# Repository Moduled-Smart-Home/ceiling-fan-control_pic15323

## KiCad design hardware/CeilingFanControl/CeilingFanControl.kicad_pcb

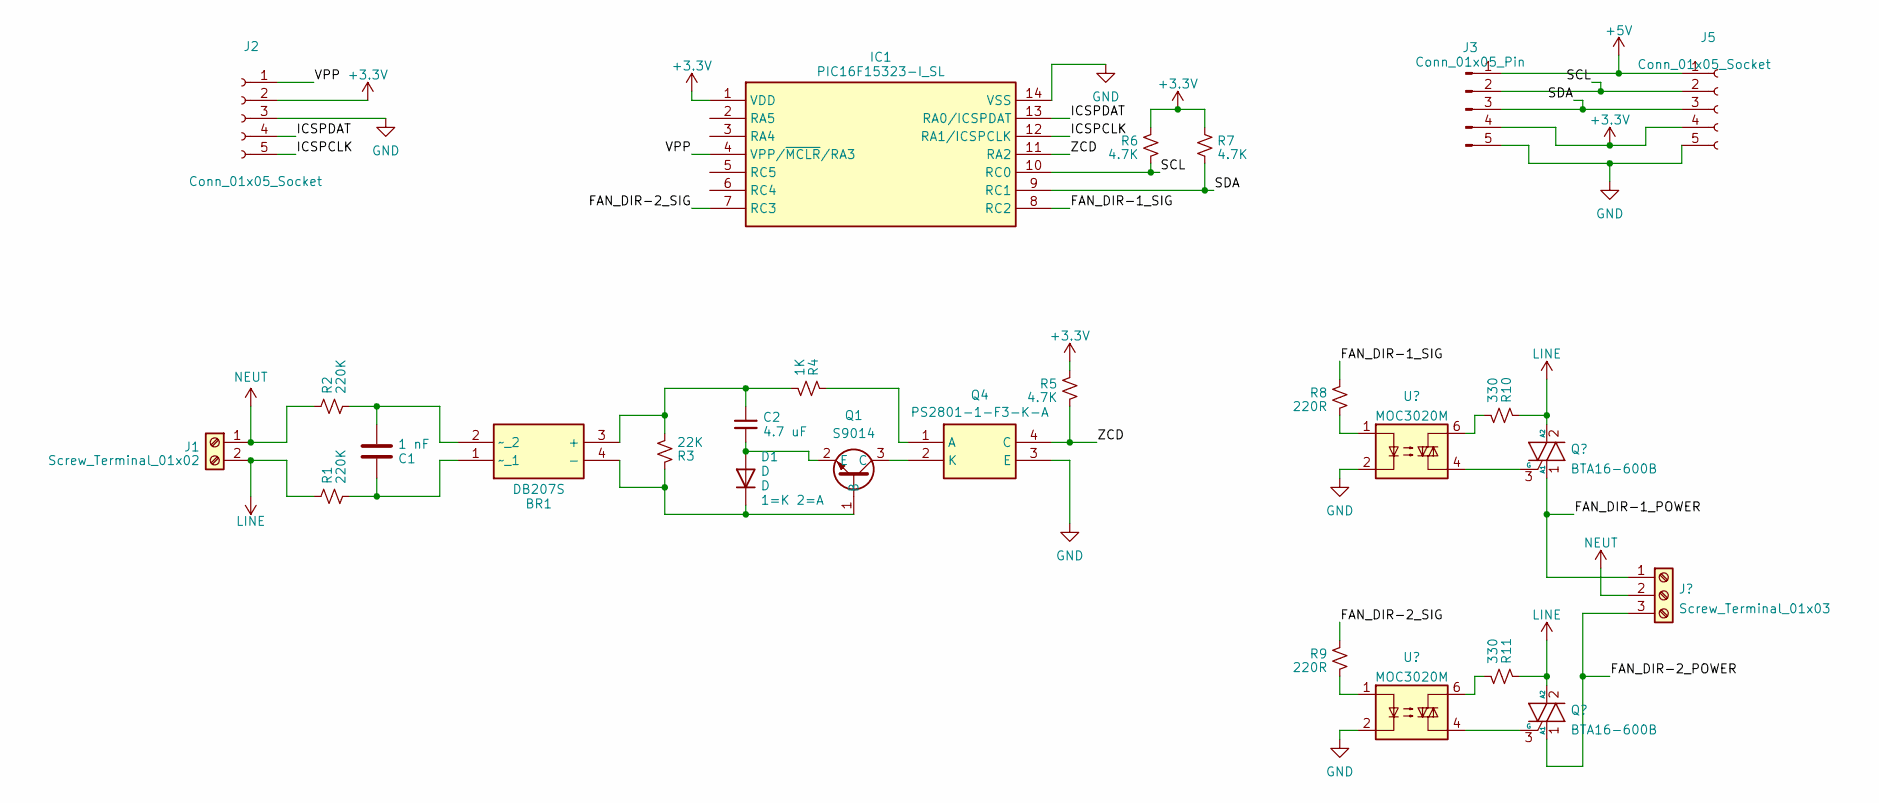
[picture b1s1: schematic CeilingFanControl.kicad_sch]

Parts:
BR1: DB207S; SOP510P1015X375-4N; Manufacturer_Part_Number DB207S
C1: 1 nF; C_0805_2012Metric
C2: 4.7 uF; C_0805_2012Metric
D1: D; D_SOD-123
IC1: PIC16F15323-I_SL; SOIC127P600X175-14N; Manufacturer_Part_Number PIC16F15323-I/SL; Mouser Part Number 579-PIC16F15323-I/SL
J1: Screw_Terminal_01x02; KF3012P
J2: Conn_01x05_Socket; PinHeader_1x05_P2.54mm_Vertical
J3: Conn_01x05_Pin; PinHeader_1x05_P2.54mm_Horizontal
J4: Screw_Terminal_01x03; KF3013P
J5: Conn_01x05_Socket; PinSocket_1x05_P2.54mm_Horizontal
Q1: S9014; SOT65P230X110-3N; Manufacturer_Part_Number S9014W
Q2, Q3: BTA16-600B; TO-220-3_Vertical
Q4: PS2801-1-F3-K-A; SOIC127P700X210-4N; Manufacturer_Part_Number PS2801-1-F3-K-A; Mouser Part Number 968-PS2801-1-F3-K-A
R1, R2: 220K; R_0805_2012Metric
R3: 22K; R_0805_2012Metric
R4: 1K; R_0805_2012Metric
R5, R6, R7: 4.7K; R_0805_2012Metric
R8, R9: 220R; R_0805_2012Metric
R10, R11: 330; R_2512_6332Metric_Pad1.40x3.35mm_HandSolder
U2, U3: MOC3020M; SMDIP-6_W7.62mm

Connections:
+3V3: IC1.1 (VDD), J2.2, J3.4, J5.4, R5.1, R6.1, R7.1
+5V: J3.1, J5.1
/FAN_DIR-1_POWER: J4.1, Q2.1 (A1)
/FAN_DIR-1_SIG: IC1.8 (RC2), R8.1
/FAN_DIR-2_POWER: J4.3, Q3.1 (A1)
/FAN_DIR-2_SIG: IC1.7 (RC3), R9.1
/ICSPCLK: IC1.12 (RA1/ICSPCLK), J2.5
/ICSPDAT: IC1.13 (RA0/ICSPDAT), J2.4
/SCL: IC1.10 (RC0), J3.2, J5.2, R6.2
/SDA: IC1.9 (RC1), J3.3, J5.3, R7.2
/VPP: IC1.4 (VPP/~MCLR/RA3), J2.1
/ZCD: IC1.11 (RA2), Q4.4 (C), R5.2
GND: IC1.14 (VSS), J2.3, J3.5, J5.5, Q4.3 (E), U2.2, U3.2
LINE: J1.2, Q2.2 (A2), Q3.2 (A2), R1.1, R10.1, R11.1
NEUT: J1.1, J4.2, R2.1
unnamed: BR1.3 (+), C2.1, R3.2, R4.2
unnamed: BR1.4 (-), D1.1 (K), Q1.1 (B), R3.1
unnamed: BR1.1 (~_1), C1.2, R1.2
unnamed: BR1.2 (~_2), C1.1, R2.2
unnamed: C2.2, D1.2 (A), Q1.2 (E)
unnamed: Q1.3 (C), Q4.2 (K)
unnamed: Q2.3 (G), U2.4
unnamed: Q3.3 (G), U3.4
unnamed: Q4.1 (A), R4.1
unnamed: R8.2, U2.1
unnamed: R9.2, U3.1
unnamed: R10.2, U2.6
unnamed: R11.2, U3.6

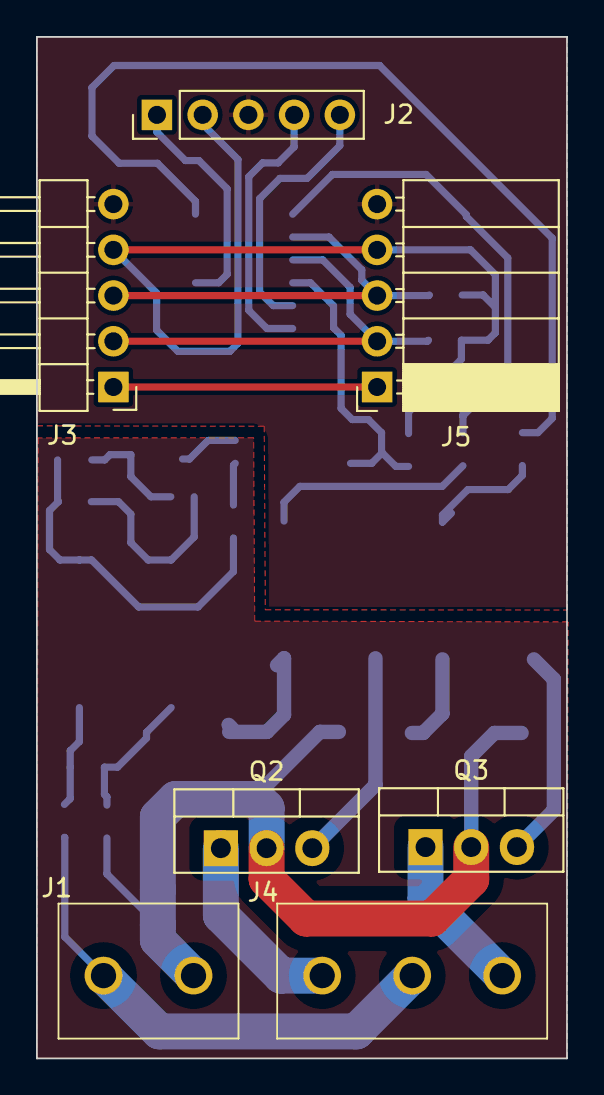
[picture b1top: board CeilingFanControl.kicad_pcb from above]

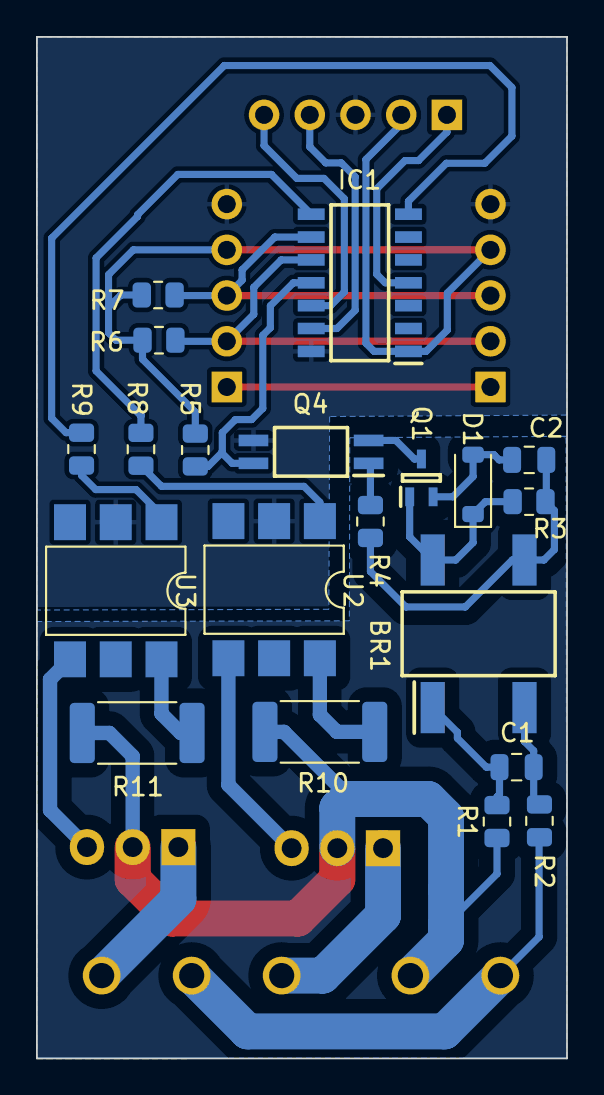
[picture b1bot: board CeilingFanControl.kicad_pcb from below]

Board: 2 copper layers, 29.4 x 56.8 mm, 27 parts (20 on the bottom side), 28 nets.

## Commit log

2024-01-04 first commit firmware
2024-01-07 first commit hardware
2024-01-08 Remove interrupt_manager.c from .gitignore
2024-12-15 commit before system update
